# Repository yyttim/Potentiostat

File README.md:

# Potentiostat
Open source simple potentiostat

## 2022.12.6

### Curent progress

We decided to ditch KiCAD and use Altium Designer for the rest of the work

The files for the Altium Designer version are in the "Potentiostat" folder

### Next step

Optimize schematic

Draw PCB layout

## 2022.11.25

### Curent progress

Completed the packaging of each chip

Updated PCB from schematic

### Next step

Adjust the position of each component

Complete wiring

## 2022.11.17

### Current progress

Completed the packaging of each component

Adjusted the parameters of each capacitor

### Next step

Continue to correct problems in the schematic

Complete PCB layout

## 2022.11.6

### Current progress

Replaced some of the original components with components from the pspice library

Completed the construction of the equivalent circuit of the electrodes

Completed the spice model construction of most of the components

### Next step

Find the spice model of the remaining components

Run circuit simulation

## 2022.10.30

### Current progress

Completed the drawing of the circuit schematic

### Next step

Run circuit simulation

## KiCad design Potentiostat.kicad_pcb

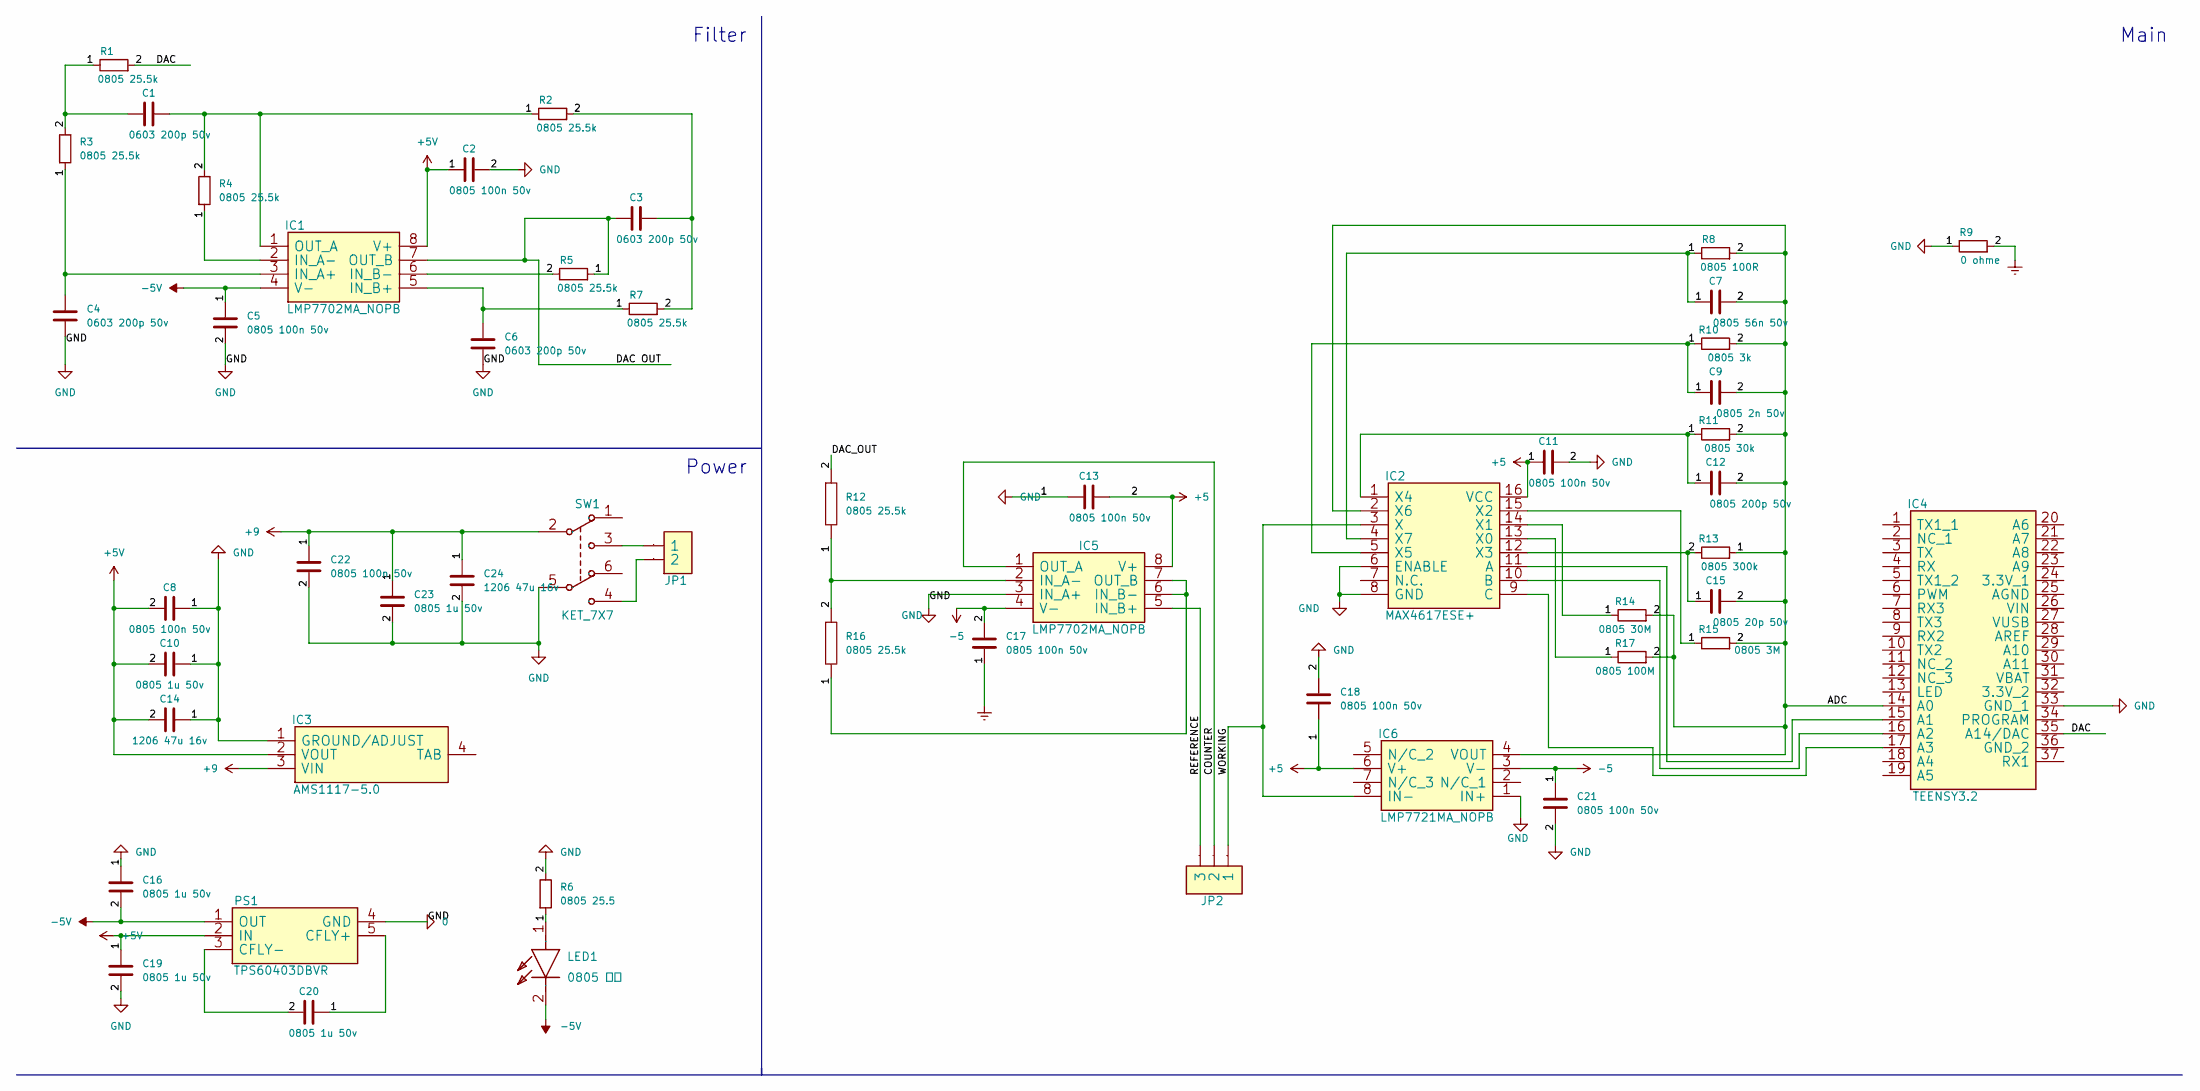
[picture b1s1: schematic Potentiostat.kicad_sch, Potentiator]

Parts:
C1, C3, C4, C6: 0603 200p 50v; C_0805_2012Metric
C2, C5, C8, C11, C13, C17, C18, C21, C22: 0805 100n 50v; C_0805_2012Metric
C7: 0805 56n 50v; C_0805_2012Metric
C9: 0805 2n 50v; C_0805_2012Metric
C10, C16, C19, C20, C23: 0805 1u 50v; C_0805_2012Metric
C12: 0805 200p 50v; C_0805_2012Metric
C14, C24: 1206 47u 16v; C_1206_3216Metric
C15: 0805 20p 50v; C_0805_2012Metric
IC1, IC5: LMP7702MA_NOPB
IC2: MAX4617ESE+
IC3: AMS1117-5.0
IC4: TEENSY3.2
IC6: LMP7721MA_NOPB
JP1, JP2: (no value)
LED1: 0805 红色; LED_0805_2012Metric
PS1: TPS60403DBVR
R1, R2, R3, R4, R5, R7, R12, R16: 0805 25.5k; R_0805_2012Metric
R6: 0805 25.5; R_0805_2012Metric
R8: 0805 100R; R_0805_2012Metric
R9: 0 ohme; R_0805_2012Metric
R10: 0805 3k; R_0805_2012Metric
R11: 0805 30k; R_0805_2012Metric
R13: 0805 300k; R_0805_2012Metric
R14: 0805 30M; R_0805_2012Metric
R15: 0805 3M; R_0805_2012Metric
R17: 0805 100M; R_0805_2012Metric
SW1: KET_7X7

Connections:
+5: C1.1, C1.2, C2.1, C2.2, C3.1, C3.2, C4.1, C4.2, C5.1, C5.2, C6.1, C6.2, C7.1, C7.2, C8.1, C8.2, C9.1, C9.2, C10.1, C10.2, C11.1, C11.2, C12.1, C12.2, C13.1, C13.2, C14.1, C14.2, C15.1, C15.2, C16.1, C16.2, C17.1, C17.2, C18.1, C18.2, C19.1, C19.2, C20.1, C20.2, C21.1, C21.2, C22.1, C22.2, C23.1, C23.2, C24.1, C24.2, IC1.1 (OUT_A), IC1.2 (IN_A-), IC1.3 (IN_A+), IC1.4 (V-), IC1.5 (IN_B+), IC1.6 (IN_B-), IC1.7 (OUT_B), IC1.8 (V+), IC2.1 (X4), IC2.2 (X6), IC2.4 (X7), IC2.5 (X5), IC2.6 (ENABLE), IC2.8 (GND), IC2.12 (X3), IC2.13 (X0), IC2.14 (X1), IC2.15 (X2), IC2.16 (VCC), IC3.1 (GROUND/ADJUST), IC3.2 (VOUT), IC3.3 (VIN), IC4.14 (A0), IC4.33 (GND_1), IC4.35 (A14/DAC), IC5.2 (IN_A-), IC5.3 (IN_A+), IC5.4 (V-), IC5.6 (IN_B-), IC5.7 (OUT_B), IC5.8 (V+), IC6.1 (IN+), IC6.3 (V-), IC6.4 (VOUT), IC6.6 (V+), LED1.1 (A), LED1.2 (K), PS1.1 (OUT), PS1.2 (IN), PS1.3 (CFLY-), PS1.4 (GND), PS1.5 (CFLY+), R1.1, R1.2, R2.1, R2.2, R3.1, R3.2, R4.1, R4.2, R5.1, R5.2, R6.1, R6.2, R7.1, R7.2, R8.1, R8.2, R9.1, R9.2, R10.1, R10.2, R11.1, R11.2, R12.1, R12.2, R13.1, R13.2, R14.1, R14.2, R15.1, R15.2, R16.1, R16.2, R17.1, R17.2, SW1.2 (COM2), SW1.5 (COM2)
/COUNTER: IC5.1 (OUT_A), JP2.2
/REFERENCE: IC5.5 (IN_B+), JP2.3
/WORKING: IC2.3 (X), IC6.8 (IN-), JP2.1
unnamed: IC2.9 (C), IC4.17 (A3)
unnamed: IC2.10 (B), IC4.16 (A2)
unnamed: IC2.11 (A), IC4.15 (A1)
unnamed: JP1.1, SW1.3 (NO1)
unnamed: JP1.2, SW1.4 (NO2)

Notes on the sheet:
Filter
Main
Power

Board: 2 copper layers, 52 parts (0 on the bottom side), 9 nets, no tracks yet.

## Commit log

2022-11-17 Create sym-lib-table
2022-11-17 Create fp-info-cache
2022-11-17 Update fp-info-cache
2022-11-25 Create fp-lib-table
